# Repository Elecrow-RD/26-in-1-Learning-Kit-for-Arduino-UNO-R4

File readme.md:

## Menu
### 1, Product picture
### 2, Product version number
### 3, product information
### 4, Use the driver module
### 5,Quick Start
### 6,Folder structure.
### 7,Pin definition

### 1, Product picture

#### 2, Product version number

|      | Hardware | Software | Remark |
| ---- | -------- | -------- | ------ |
| 1    | V1.0     | V1.0     | latest |
### 3, product information

| Main Processor        | Arduino UNO R4                                               |
| --------------------- | ------------------------------------------------------------ |
| CPU/SoC               | RA4M1(Arm® Cortex-M4®)                                       |
| System memory         | 32 kB SRAM                                                   |
| Storage               | 256 kB Flash Memory                                          |
| Bluetooth             | Bluetooth 5                                                  |
| Wi-Fi                 | Wi-Fi® support with 802.11 b/g/n standarBit rate at up to 150 Mbps2.4 GHz band |
| Interface             | 6\*D Interfaces<br />4\*A Interfaces<br />4\*I2C Interfaces<br />4\* Pin header<br />2\*3pin connectors<br />1*Stepper Interface |
| Button                | Reset                                                        |
| LED indicator light   | 12*8 LED dot matrix                                          |
| Power input           | 5 V                                                          |
| Shell material        | Plastic Box                                                  |
| Size                  | 278\*200*43（mm）                                            |
| Net Weight            | 600g                                                         |
| Operating temperature | 0°C to 60°C                                                  |
| Storage temperature   | 0°C to 60°C                                                  |

### 4, Use the driver module

| Name     | dependency library                           |
| -------- | -------------------------------------------- |
| IRremote | Arduino-IRremote-master <br />version: 4.5.0 |
| LSM6DS3  | Arduino_LSM6DS3-master<br />version=1.0.3    |
| BH1750   | BH1750<br />version: 1.3.0                   |

### 5,Quick Start
### Arduino IDE starts

1.Download the library files used by this product to the 'libraries' folder.

C:\Users\Documents\Arduino\libraries\

2.Open the Arduino IDE and install the Uno development board.

3.Open the code configuration environment and burn it

### 6,Folder structure.

|--Eagle_SCH&PCB: Contains **Eagle CAD** schematic (`.sch`) and PCB layout (`.brd`) files. These are used for circuit design and PCB manufacturing.

|--Single Module Example:Examples of individual modules.

|--lesson_code: Provides  code and projects to demonstrate how to use the hardware and libraries. These examples help users get started quickly.

|--libraries: Includes necessary libraries required for compiling and running the project. These libraries provide drivers and additional functionalities for the hardware.

### 7,Pin definition

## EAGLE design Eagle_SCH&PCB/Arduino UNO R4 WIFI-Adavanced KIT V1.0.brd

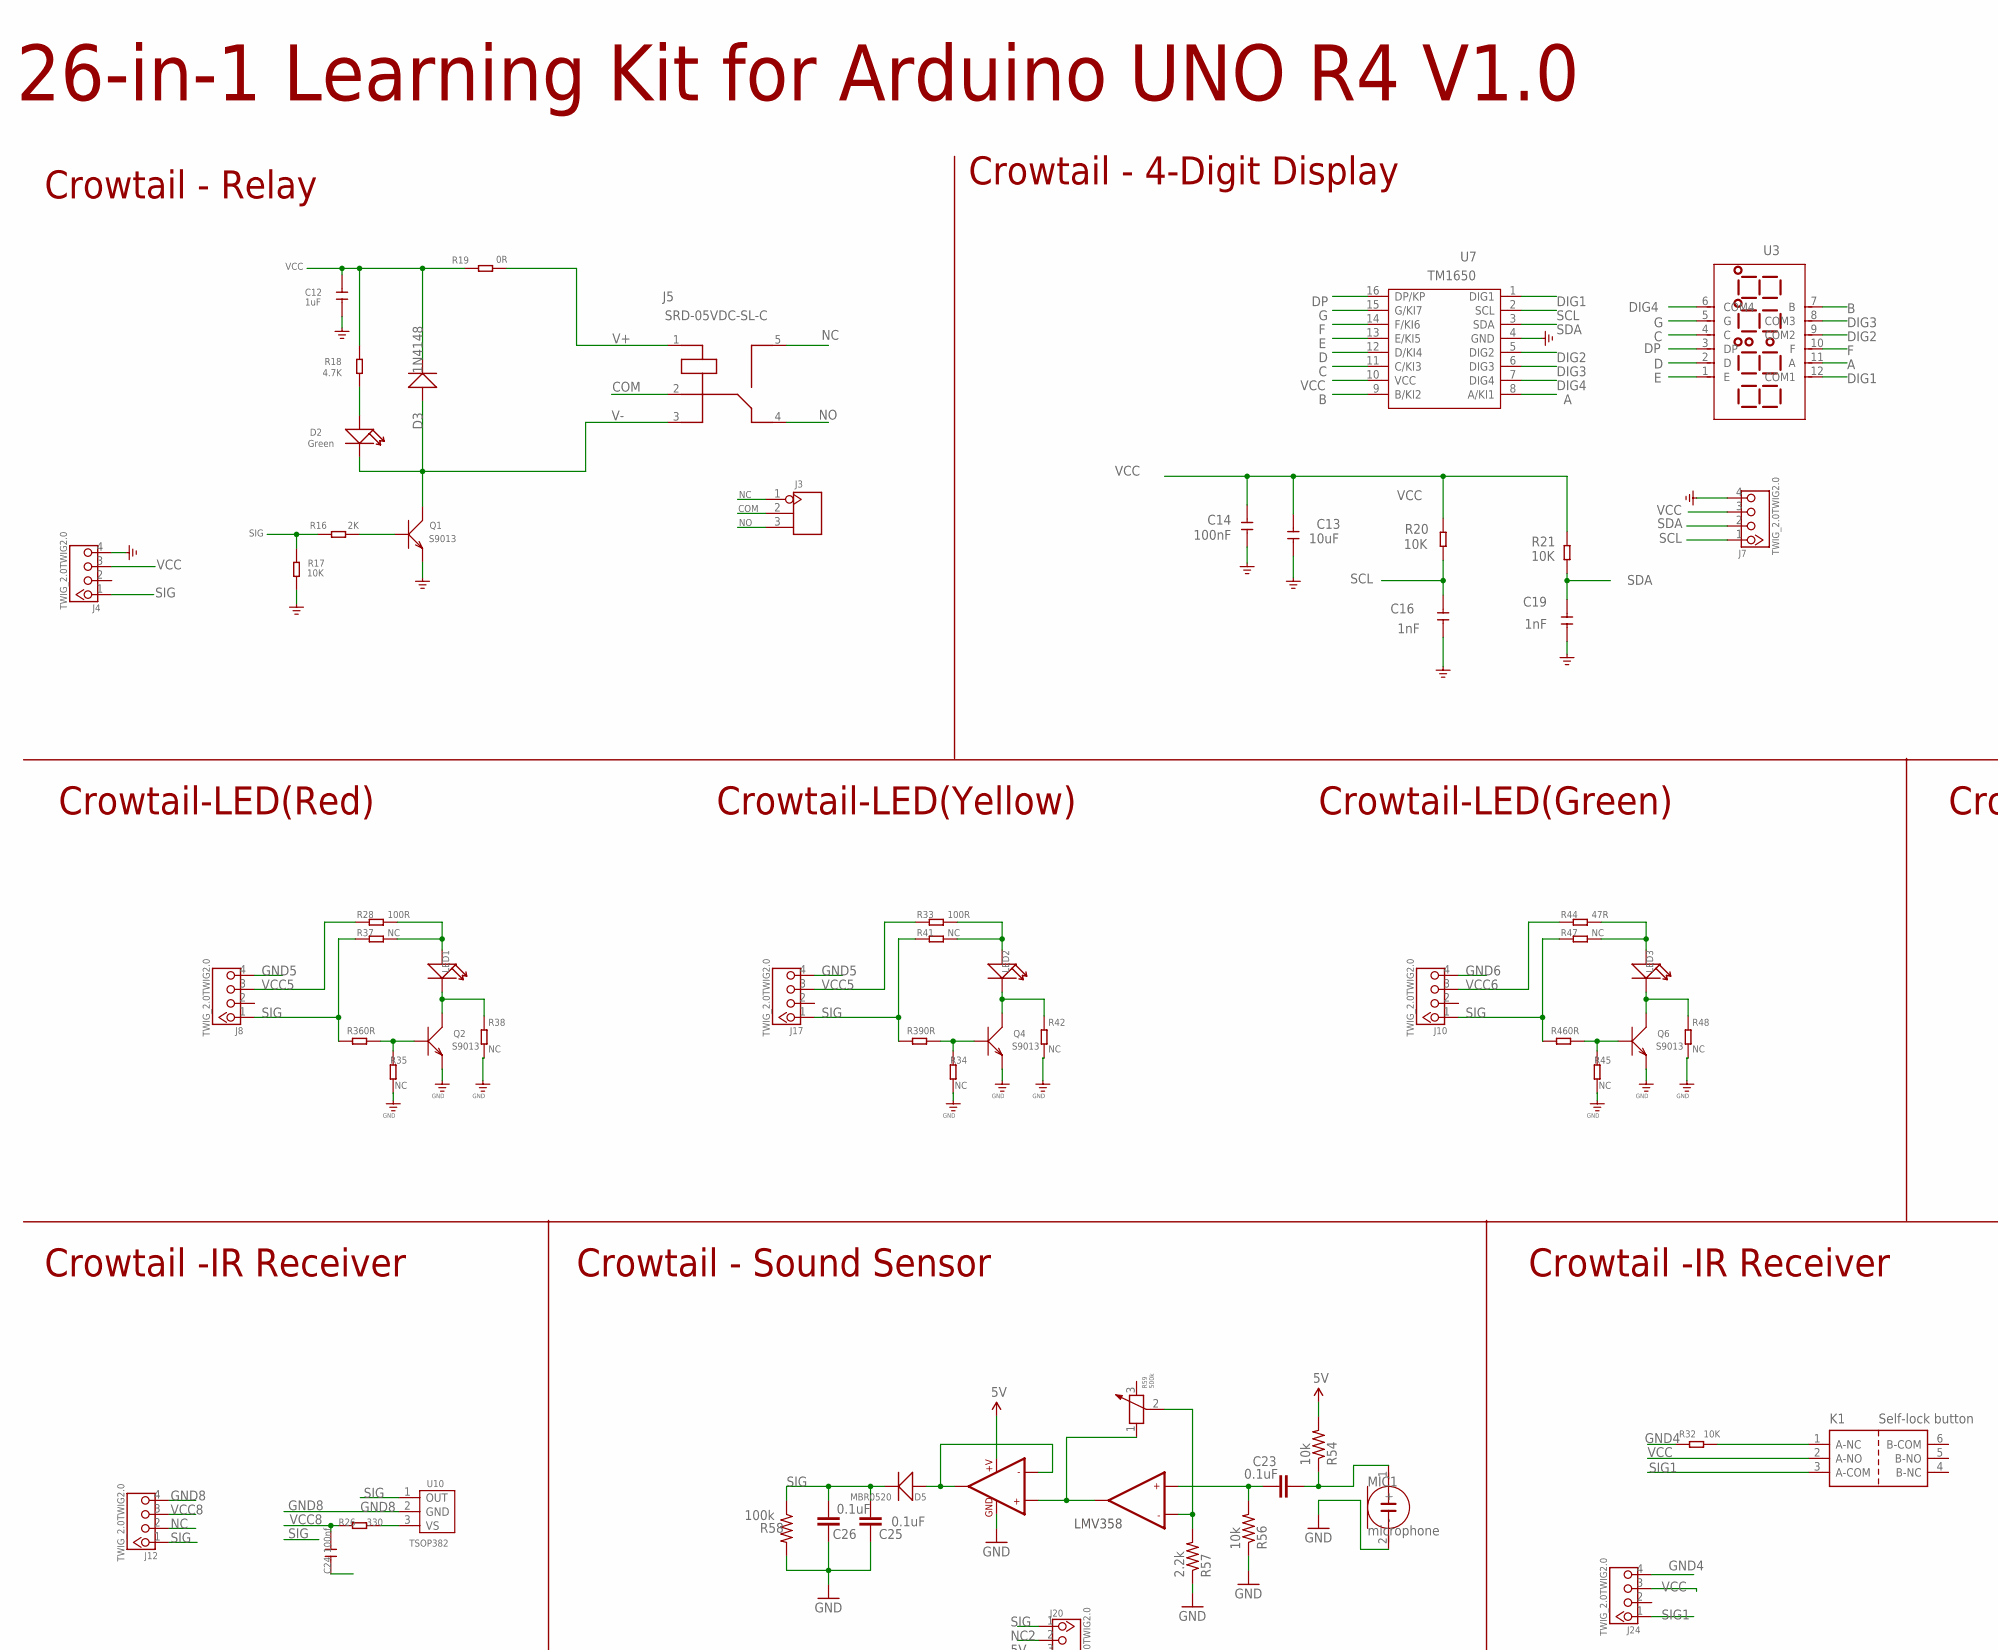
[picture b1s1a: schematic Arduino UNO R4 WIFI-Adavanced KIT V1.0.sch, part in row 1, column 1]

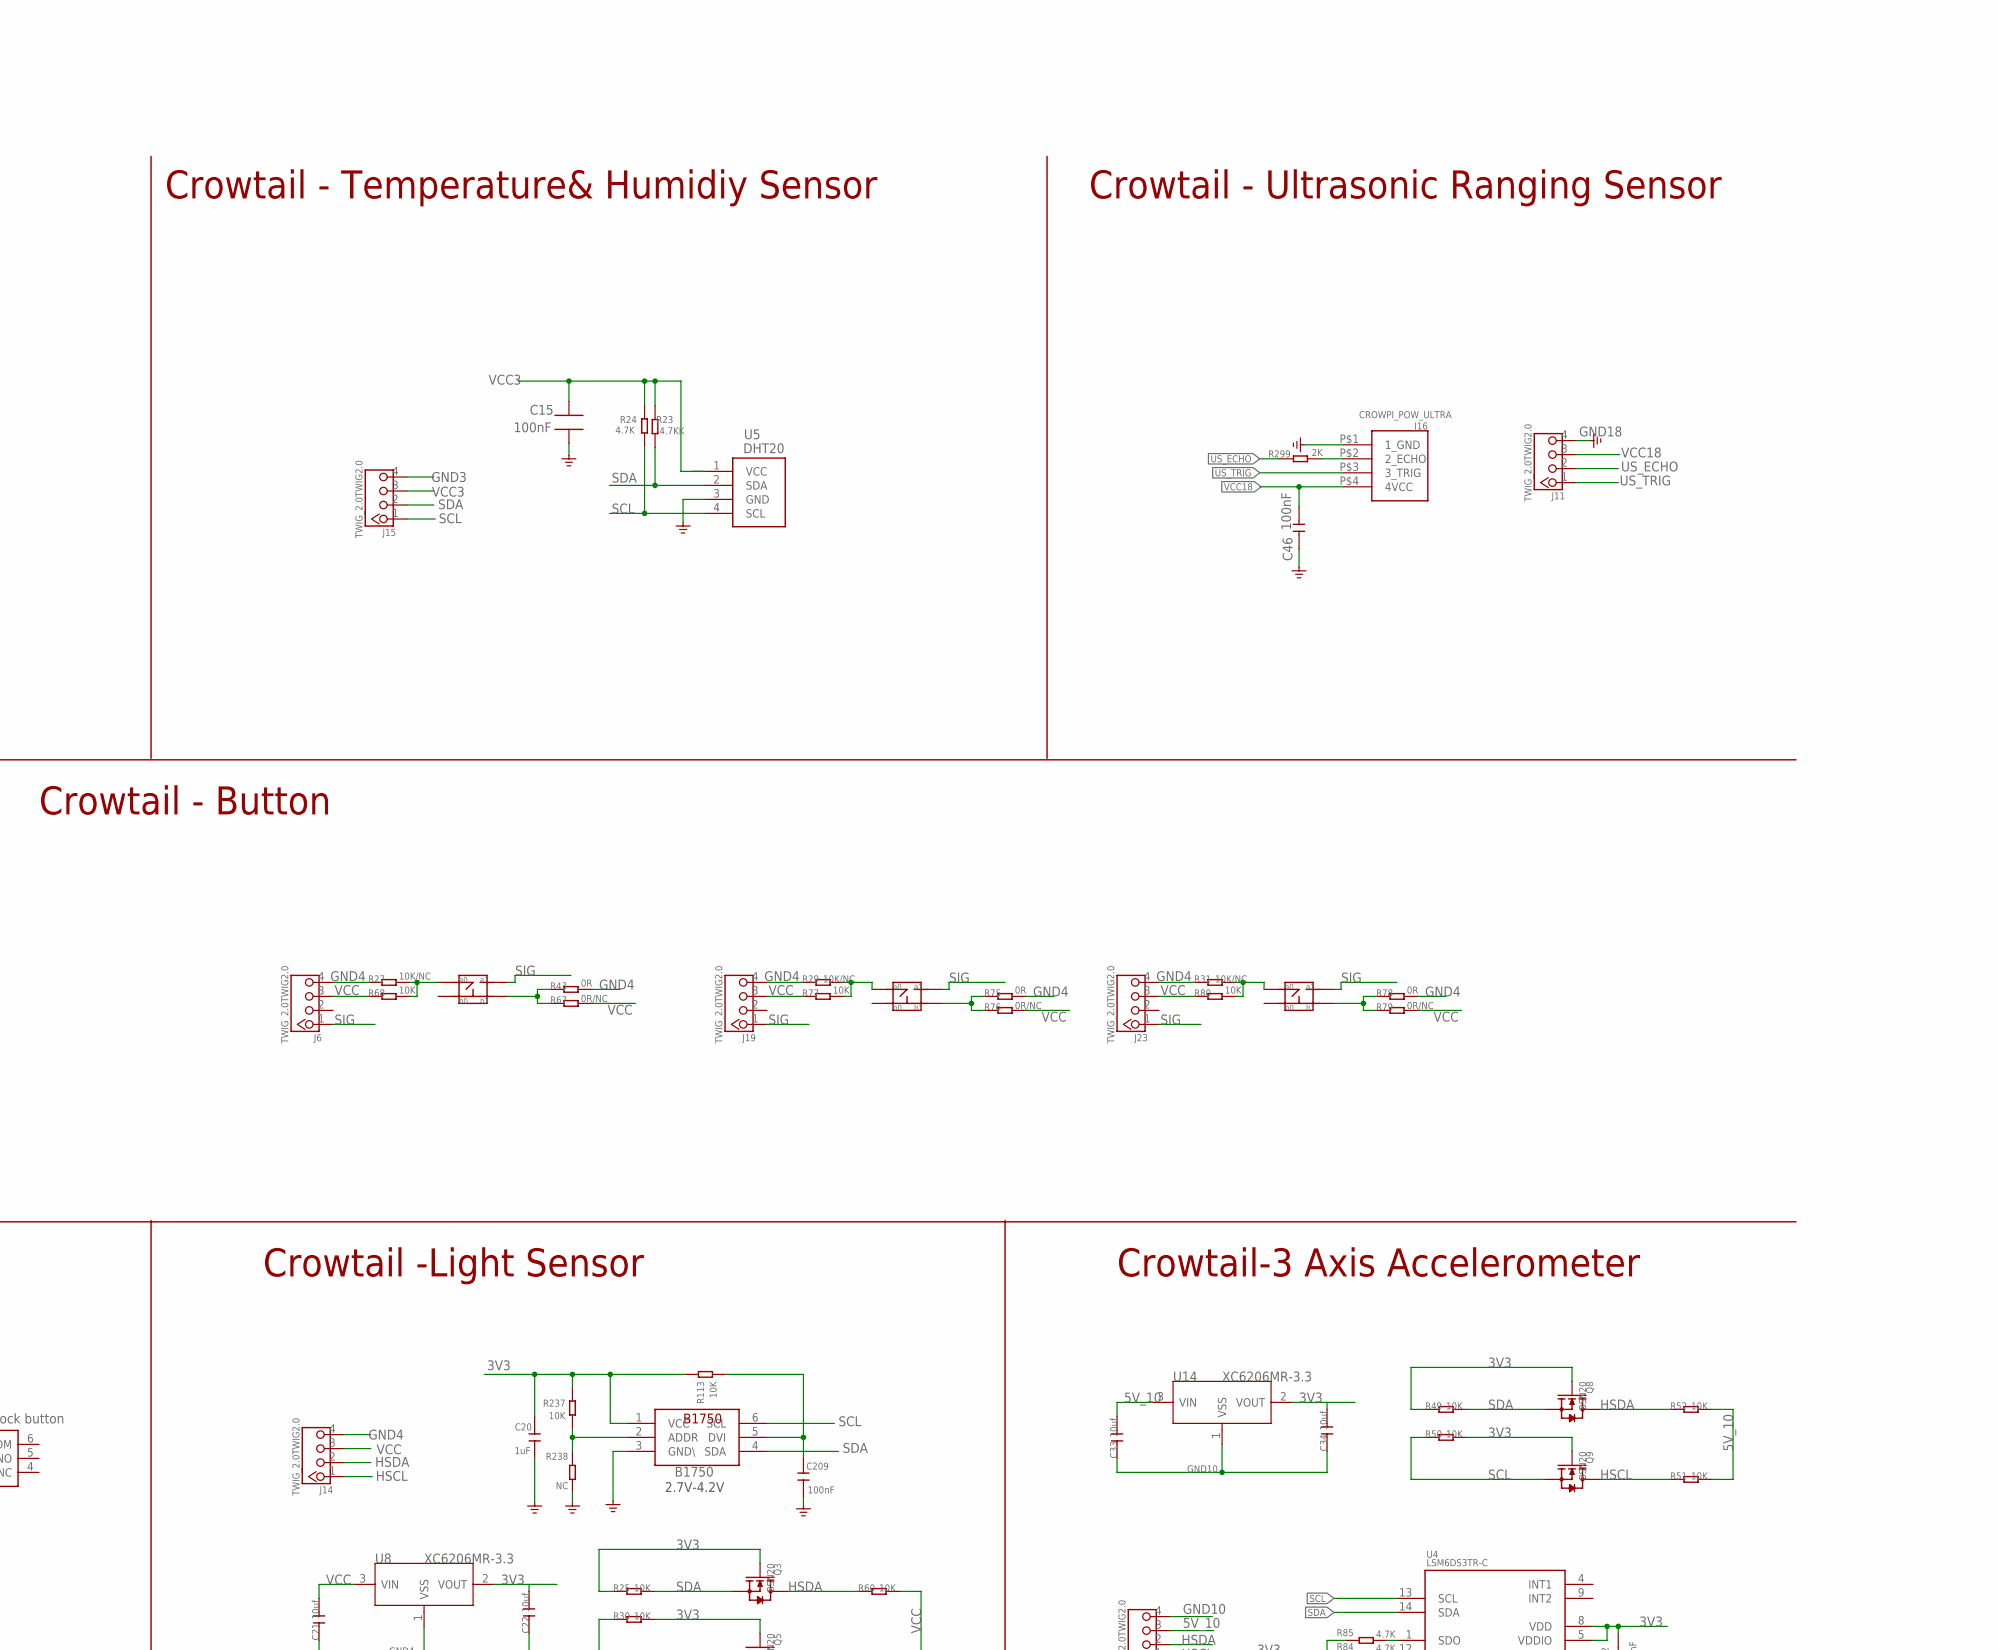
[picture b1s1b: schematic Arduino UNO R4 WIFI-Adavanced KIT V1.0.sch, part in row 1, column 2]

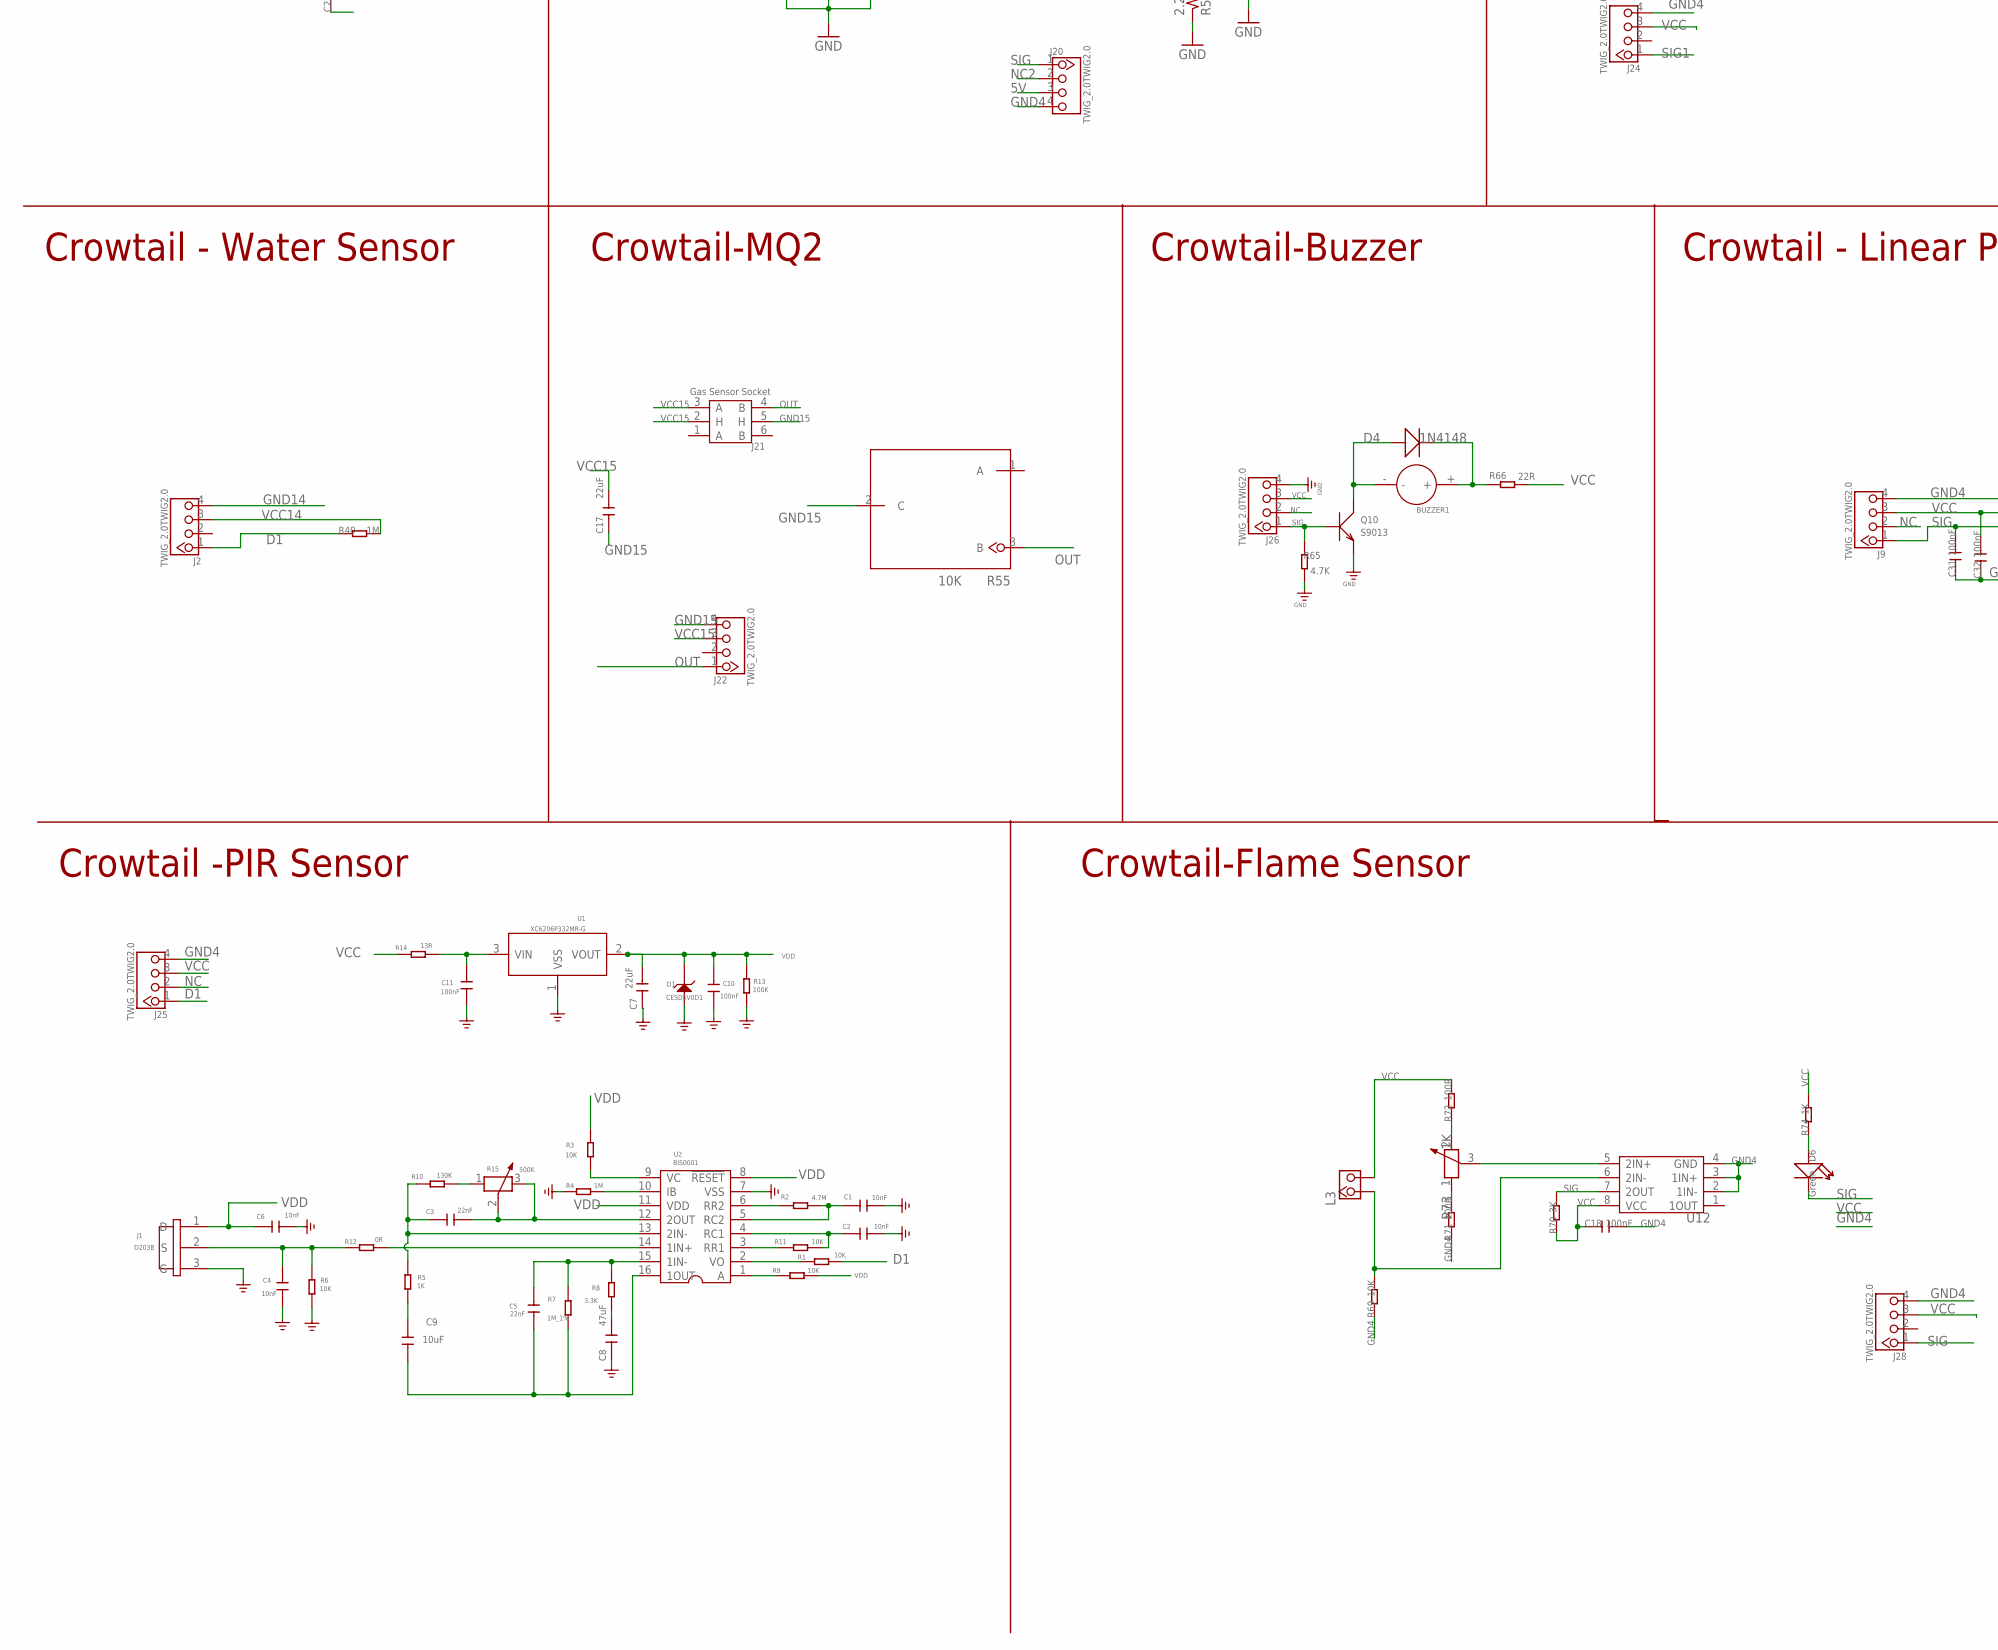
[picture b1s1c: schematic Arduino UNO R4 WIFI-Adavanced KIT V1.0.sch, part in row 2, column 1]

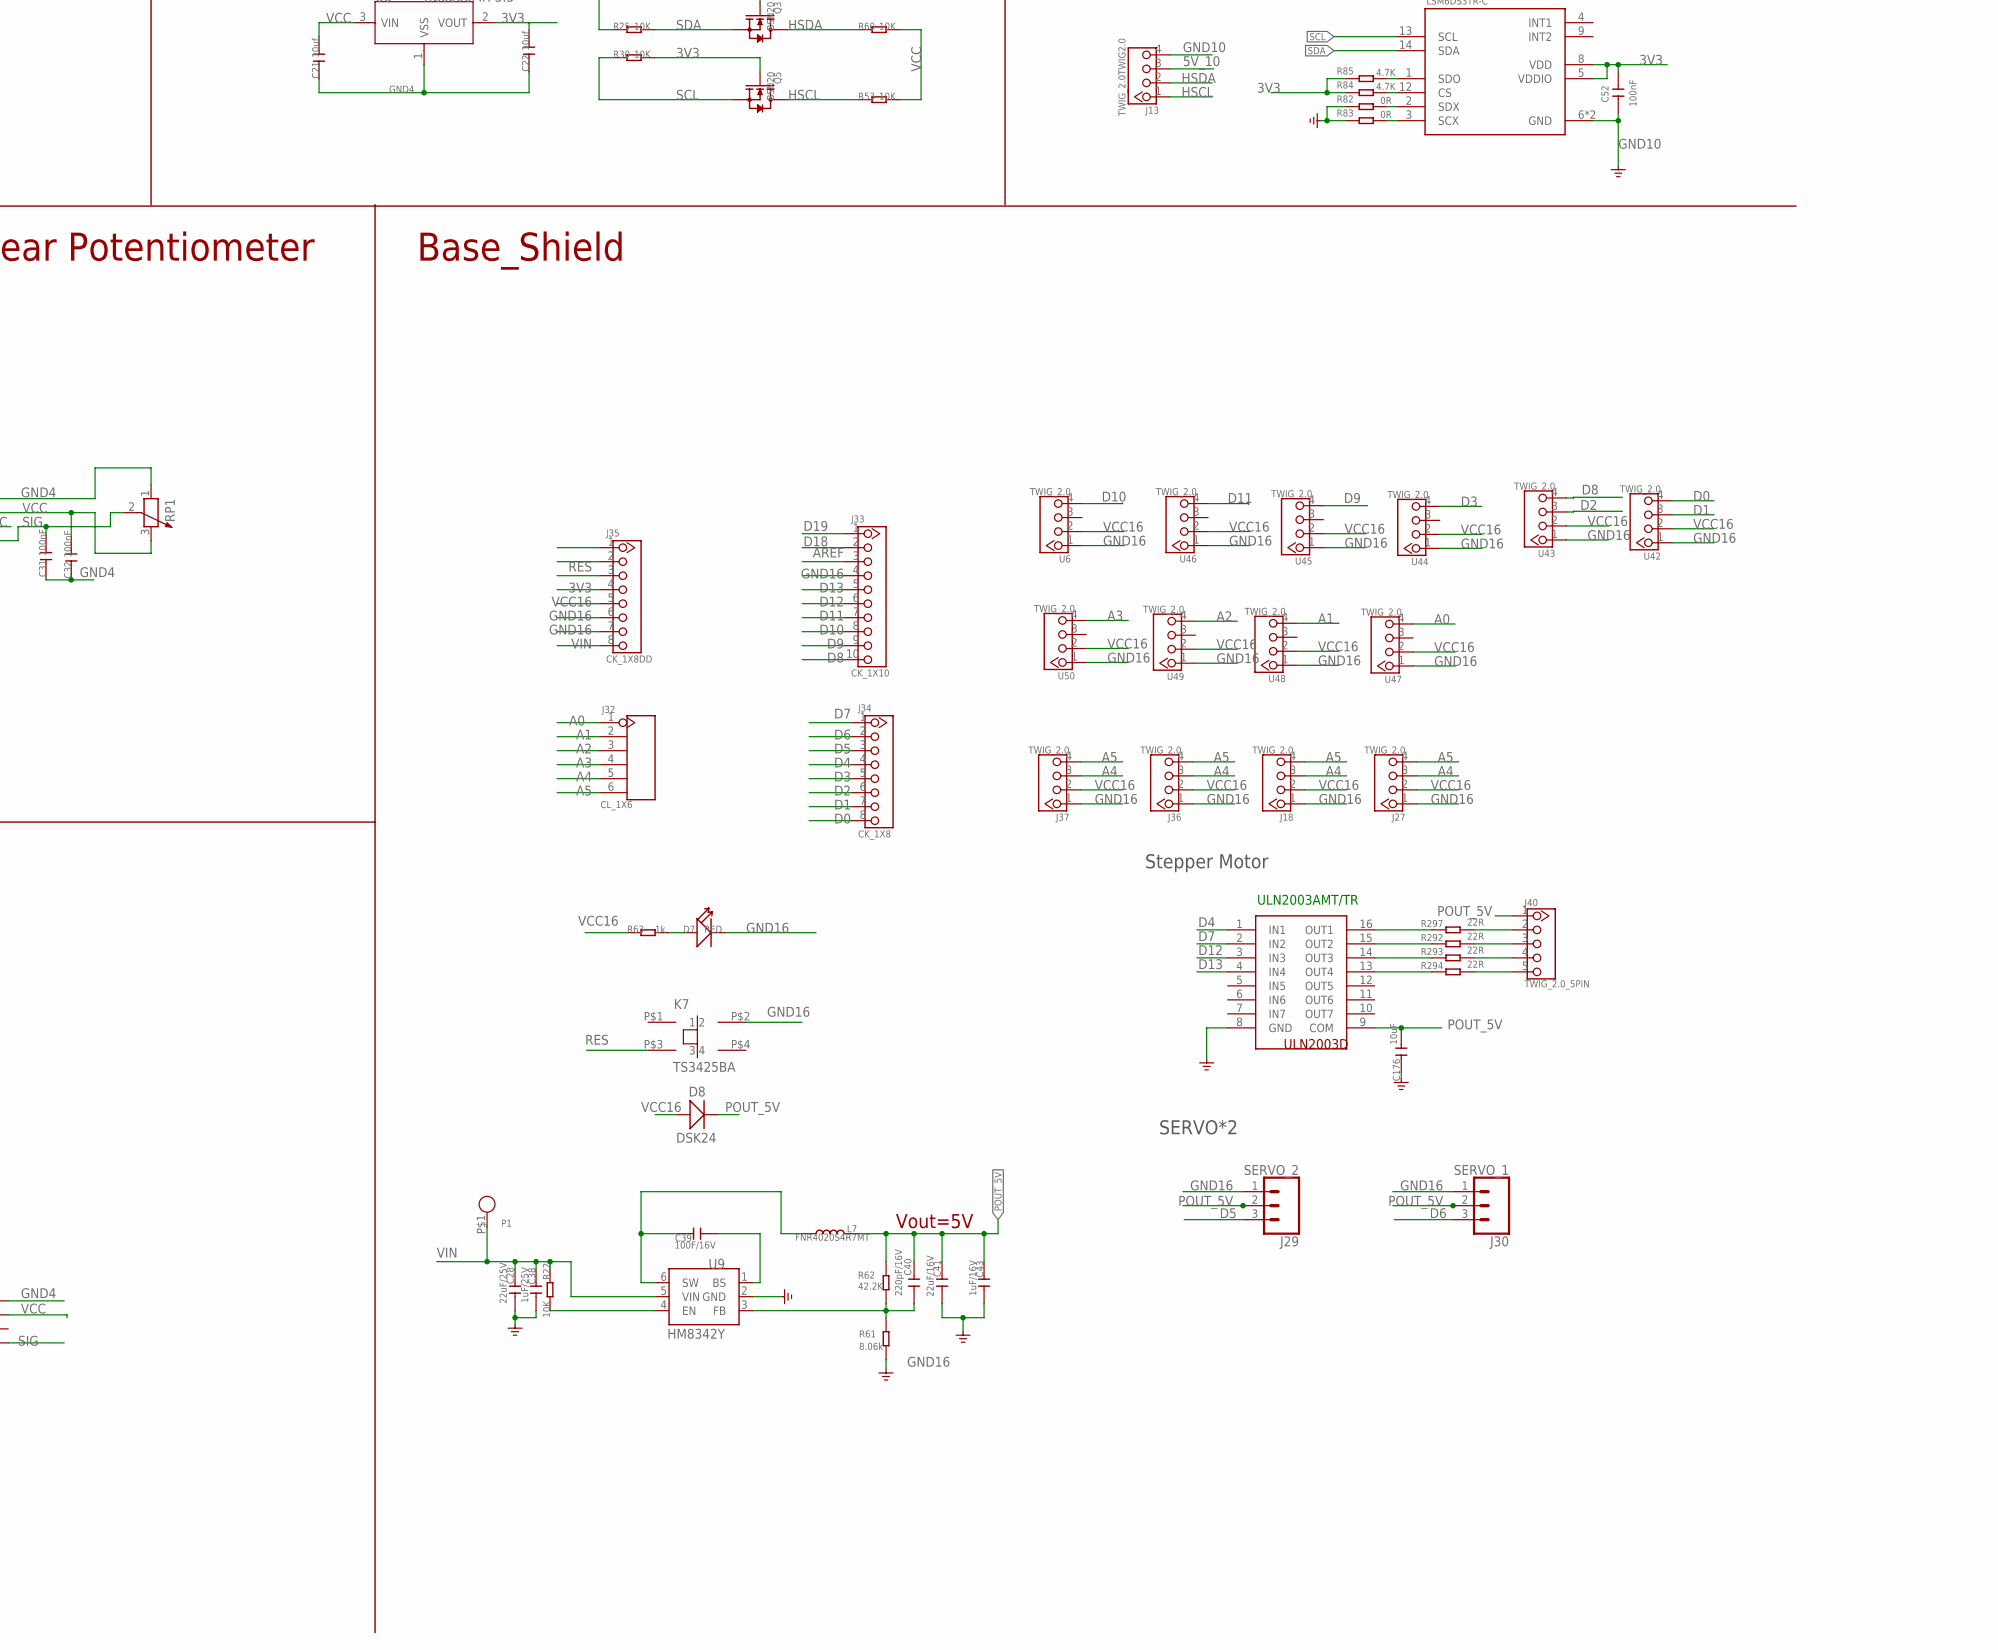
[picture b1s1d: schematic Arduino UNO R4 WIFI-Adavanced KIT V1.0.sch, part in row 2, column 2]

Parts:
BUZZER1: BUZZER-YMD12065; 2P-7.6-D12X6.5H
C1, C2, C4, C6: 10nF; C0603
C3, C5: 22nF; C0603
C7, C17: 22uF; C0805
C8: 47uF; C0805
C9: 10uF; 0603
C10, C11, C14, C18, C31, C32, C46, C52, C209: 100nF; C0603
C12: 1uF; 0603
C13: 10uF; C0603
C15: 100nF; 0603
C16, C19: 1nF; C0603
C20: 1uF; C0603
C21, C22, C33, C34: 10uf; C0603
C23, C25, C26: 0.1uF; 0603-CAP
C24: 100nf; C0603
C28: 22uF/25V; C0805
C38: 1uF/25V; C0603
C39: 100F/16V; C0402
C40: 220pF/16V; C0402
C41: 22uF/16V; C0603
C43: 1uF/16V; C0603
C176: 10uF; C0805
D1: CESD5V0D1; SOD123-2.7X1.6@1
D2, D6: Green; LED-0603
D3, D4: 1N4148; D_SOD123
D5: MBR0520; SOD123-2.7X1.6
D7: RED; LED-0805
D8: DSK24; D_SOD123FL
J1: D203B; 3P-D8.1MM
J2, J4, J6, J7, J8, J9, J10, J11, J12, J13, J14, J15, J17, J19, J20, J22, J23, J24, J25, J26, J28: TWIG_2.0TWIG2.0; TWIG_2.0
J3: SCREW-TERMINAL-3P'5.08'; 3P-5.08
J5: SRD-05VDC-SL-C; A_XBJ_SMART_PUMP_SONGLE_RELAY
J16: CROWPI_POW_ULTRA
J18, J27, J36, J37: TWIG_2.0; 2.0_1X4
J21: Gas Sensor Socket; MQ2
J29: SERVO_2; 1X03
J30: SERVO_1; 1X03
J32: CL_1X6; CK_1X6
J33: CK_1X10
J34: CK_1X8
J35: CK_1X8DD; CK_1X8
J40: TWIG_2.0_5PIN; TWIG-2.0-5PIN
K1: Self-lock button; 6P-2CH-8X8
K2, K3, K4: 12X12
K7: TS3425BA; SMD_KEY4.2*3.*.2.5
L3: HEADER_1X2_2.54; CK_1*2
L7: FNR4020S4R7MT; L_4X4
LED1, LED2, LED3: LED-6MM; LED-2P-2.54-6MM
MIC1: microphone; 2P-D8.9MM
P1: PADPAD-1.0MM; PAD-1.0MM
Q1, Q2, Q4, Q6: S9013; SOT23@1
Q3, Q5, Q8, Q9: BSN20; SOT23@2
Q10: S9013; DISCRETE_SOT23
R1, R3, R6, R9, R11, R17, R20, R21, R25, R30, R32, R49, R50, R51, R52, R53, R60, R68, R69, R77, R80, R113, R237: 10K; R0603
R2: 4.7M; R0603
R4: 1M; R0603
R5, R74: 1K; R0603
R7: 1M_1%; R0603
R8: 3.3K; R0603
R10: 130K; R0603
R12, R19, R36, R39, R43, R46, R75, R78, R82, R83: 0R; R0603
R13: 100K; R0603
R14: 13R; R0603
R15: 500K; 3P-SMD-SQUA-3.6X3.3
R16, R299: 2K; R0603
R18, R65, R84, R85: 4.7K; R0603
R22: 10K; R0402
R23: 4.7KK; 0603
R24: 4.7K; 0603
R26: 330; R0603
R27, R29, R31: 10K/NC; R0603
R28, R33, R71, R72: 100R; R0603
R34, R35, R37, R38, R41, R42, R45, R47, R48, R238: NC; R0603
R40: 1M; 0603
R44: 47R; R0603
R54, R56: 10k; 0603-RES
R55: 10K; PACKAGE__RESISTANCE
R57: 2.2k; 0603-RES
R58: 100k; 0603-RES
R59: 500k; 3P-SMD-SQUA-3.6X3.3
R61: 8.06k; R0402
R62: 42.2K; R0402
R63: 1k; 0603
R66, R292, R293, R294, R297: 22R; R0603
R67, R76, R79: 0R/NC; R0603
R70: 3K; R0603
R73: 1K; 3P-SQUA-7X6.8
RP1: R-POTENTIOMETER; 3P-SQUA-45.6X10X5.8H
U1: XC6206P332MR-G; SOT23
U2: BIS0001; SOP16
U3: MODULE_LED-4BIT-7SEG/CLOCK; MODULE_7-4-SEG/CLOCK-2.54-32.2*10.2*5.8
U4: LSM6DS3TR-C; LGA-14L
U5: DHT20
U6, U42, U43, U44, U45, U46, U47, U48, U49, U50: TWIG_2.0; 2.0_1X4
U7: TM1650; SO16
U8, U14: XC6206MR-3.3; SOT23
U9: HM8342Y; SOT23-6L
U10: TSOP382; 3P-2.54-4.8X5X6.95H
U11: LMV358; SO08
U12: LM293D; SOIC8-6.0
U114: ULN2003AMT/TR; SOP65P640X120-16N
U121: BH1750; B1750

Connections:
3V3: C20.2, C22.2, C34.2, C52.2, J35.4, Q3.1 (G), Q5.1 (G), Q8.1 (G), Q9.1 (G), R25.1, R30.2, R49.1, R50.2, R84.1, R85.1, R113.2, R237.2, U4.5 (VDDIO), U4.8 (VDD), U8.2 (VOUT), U14.2 (VOUT), U121.1 (VCC)
5V: J20.3, R54.2, U11.8 (+V)
5V_10: C33.2, J13.3, R51.2, R52.2, U14.3 (VIN)
A: U3.11 (A), U7.8 (A/KI1)
A0: J32.1, U47.4
A1: J32.2, U48.4
A2: J32.3, U49.4
A3: J32.4, U50.4
A4: J18.3, J27.3, J32.5, J36.3, J37.3
A5: J18.4, J27.4, J32.6, J36.4, J37.4
AREF: J33.3
B: U3.7 (B), U7.9 (B/KI2)
C: U3.4 (C), U7.11 (C/KI3)
COM: J3.2, J5.2
D: U3.2 (D), U7.12 (D/KI4)
D0: J34.8, U42.4
D1: J2.1, J25.1, J34.7, R1.1, R40.1, U42.3
D2: J34.6, U43.3
D3: J34.5, U44.4
D4: J34.4, U114.1 (IN1)
D5: J29.3, J34.3
D6: J30.3, J34.2
D7: J34.1, U114.2 (IN2)
D8: J33.10, U43.4
D9: J33.9, U45.4
D10: J33.8, U6.4
D11: J33.7, U46.4
D12: J33.6, U114.3 (IN3)
D13: J33.5, U114.4 (IN4)
D18: J33.2
D19: J33.1
DIG1: U3.12 (COM1), U7.1 (DIG1)
DIG2: U3.9 (COM2), U7.5 (DIG2)
DIG3: U3.8 (COM3), U7.6 (DIG3)
DIG4: U3.6 (COM4), U7.7 (DIG4)
DP: U3.3 (DP), U7.16 (DP/KP)
E: U3.1 (E), U7.13 (E/KI5)
F: U3.10 (F), U7.14 (F/KI6)
G: U3.5 (G), U7.15 (G/KI7)
GND3: C15.2, J15.4, U5.3 (GND)
GND4: C1.2, C2.2, C4.1, C6.1, C7.1, C8.1, C10.2, C11.1, C12.1, C13.2, C14.2, C16.2, C18.2, C19.2, C20.1, C21.1, C22.1, C25.1, C26.1, C31.1, C32.1, C209.1, D1.1, J1.3 (G), J4.4, J6.4, J7.4, J9.4, J14.4, J19.4, J20.4, J23.4, J24.4, J25.4, J26.4, J28.4, MIC1.2 (-), Q1.2 (E), Q10.2 (E), R4.1, R6.1, R13.2, R17.1, R27.1, R29.1, R31.1, R32.1, R43.2, R56.1, R57.1, R58.2, R65.1, R69.1, R71.1, R75.2, R78.2, R238.1, RP1.1, U1.1 (VSS), U2.7 (VSS), U7.4 (GND), U8.1 (VSS), U11.4 (GND), U12.2 (1IN-), U12.3 (1IN+), U12.4 (GND), U121.3 (GND\)
GND5: J8.4, J17.4, Q2.2 (E), Q4.2 (E), R34.1, R35.1, R38.2, R42.2
GND6: J10.4, Q6.2 (E), R45.1, R48.2
GND8: C24.1, J12.4, U10.2 (GND)
GND10: C33.1, C34.1, C52.1, J13.4, R82.1, R83.1, U4.6 (GND), U4.7 (GND), U14.1 (VSS)
GND14: J2.4
GND15: C17.1, J21.5 (H), J22.4, R55.2 (C)
GND16: C28.1, C38.2, C41.1, C43.2, C176.2, D7.-, J18.1, J27.1, J29.1, J30.1, J33.4, J35.6, J35.7, J36.1, J37.1, K7.P$2 (2), R61.1, U6.1, U9.2 (GND), U42.1, U43.1, U44.1, U45.1, U46.1, U47.1, U48.1, U49.1, U50.1, U114.8 (GND)
GND18: C46.2, J11.4, J16.P$1 (1_GND)
HSCL: J13.1, J14.1, Q5.3 (D), Q9.3 (D), R51.1, R53.1
HSDA: J13.2, J14.2, Q3.3 (D), Q8.3 (D), R52.1, R60.1
unnamed: R82.2, U4.2 (SDX)
unnamed: R26.2, U10.3 (VS)
unnamed: C209.2, R113.1, U121.5 (DVI)
unnamed: K2.P$1, R27.2, R68.2
unnamed: Q1.1 (B), R16.2
unnamed: D2.+, R18.2
unnamed: LED2.+, R33.2, R41.1
unnamed: LED1.+, R28.2, R37.1
unnamed: LED1.-, Q2.3 (C), R38.1
unnamed: Q2.1 (B), R35.2, R36.2
unnamed: R297.1, U114.16 (OUT1)
unnamed: K4.P$1, R31.2, R80.2
unnamed: LED2.-, Q4.3 (C), R42.1
unnamed: R11.1, U2.3 (RR1)
unnamed: LED3.+, R44.2, R47.1
unnamed: C2.1, R11.2, U2.4 (RC1)
unnamed: LED3.-, Q6.3 (C), R48.1
unnamed: Q6.1 (B), R45.2, R46.2
unnamed: R1.2, U2.2 (VO)
unnamed: R2.2, U2.6 (RR2)
unnamed: C1.1, R2.1, U2.5 (RC2)
unnamed: C3.2, R15.2 (3), R15.3 (2), U2.12 (2OUT)
unnamed: C3.1, R5.2, R10.2, U2.13 (2IN-)
unnamed: R3.2, U2.9 (VC)
unnamed: R4.2, U2.10 (IB)
unnamed: C4.2, J1.2 (S), R6.2, R12.2
unnamed: C5.1, C9.2, R7.1, U2.16 (1OUT)
unnamed: C5.2, R7.2, R8.2, U2.15 (1IN-)
unnamed: C9.1, R5.1
unnamed: C8.2, R8.1
unnamed: R9.2, U2.1 (A)
unnamed: R12.1, U2.14 (1IN+)
unnamed: C11.2, R14.1, U1.3 (VIN)
unnamed: R10.1, R15.1
unnamed: Q4.1 (B), R34.2, R39.2
unnamed: K1.1 (A-NC), R32.2
unnamed: R84.2, U4.12 (CS)
unnamed: K2.P$3, R43.1, R67.1
unnamed: R292.1, U114.15 (OUT2)
unnamed: C23.1, MIC1.1 (+), R54.1
unnamed: C23.2, R56.2, U11.5 (+IN2)
unnamed: R57.2, R59.2 (3), U11.6 (-IN2)
unnamed: D5.2 (+), U11.1 (OUT1), U11.2 (-IN1)
unnamed: R59.1, U11.3 (+IN1), U11.7 (OUT2)
unnamed: R293.1, U114.14 (OUT3)
unnamed: R294.1, U114.13 (OUT4)
unnamed: D7.+, R63.2
unnamed: BUZZER1.-, D4.+, Q10.3 (C)
unnamed: BUZZER1.+, D4.-, R66.1
unnamed: R71.2, R73.1
unnamed: R83.2, U4.3 (SCX)
unnamed: R72.1, R73.2
unnamed: R73.3, U12.5 (2IN+)
unnamed: D6.+, R74.1
unnamed: L3.1, R69.2, U12.6 (2IN-)
unnamed: K3.P$1, R29.2, R77.2
unnamed: K3.P$3, R75.1, R76.1
unnamed: R85.2, U4.1 (SDO)
unnamed: R237.1, R238.2, U121.2 (ADDR)
unnamed: J40.2, R297.2
unnamed: J40.3, R292.2
unnamed: J40.4, R293.2
unnamed: J40.5, R294.2
unnamed: J16.P$2 (2_ECHO), R299.1
unnamed: R22.1, U9.4 (EN)
unnamed: C39.1, L7.1, U9.6 (SW)
unnamed: C39.2, U9.1 (BS)
unnamed: C40.1, R61.2, R62.1, U9.3 (FB)
unnamed: K4.P$3, R78.1, R79.1
NC: J3.1, J5.5, J9.2, J12.2, J25.2, J26.2
NC2: J20.2
NO: J3.3, J5.4
OUT: J21.4 (B), J22.1, R55.3 (B)
POUT_5V: C40.2, C41.2, C43.1, C176.1, D8.-, J29.2, J30.2, J40.1, L7.2, R62.2, U114.9 (COM)
RES: J35.3, K7.P$3 (3)
SCL: C16.1, J7.1, J15.1, Q5.2 (S), Q9.2 (S), R20.2, R24.1, R30.1, R50.1, U4.13 (SCL), U5.4 (SCL), U7.2 (SCL), U121.6 (SCL)
SDA: C19.1, J7.2, J15.2, Q3.2 (S), Q8.2 (S), R21.2, R23.1, R25.2, R49.2, U4.14 (SDA), U5.2 (SDA), U7.3 (SDA), U121.4 (SDA)
SIG: C25.2, C26.2, C31.2, D5.1 (-), D6.-, J4.1, J6.1, J8.1, J9.1, J10.1, J12.1, J17.1, J19.1, J20.1, J23.1, J26.1, J28.1, K2.P$2, K3.P$2, K4.P$2, Q10.1 (B), R16.1, R17.2, R36.1, R37.2, R39.1, R41.2, R46.1, R47.2, R58.1, R65.2, R70.2, RP1.2 (3), U10.1 (OUT), U12.7 (2OUT)
SIG1: J24.1, K1.3 (A-COM)
US_ECHO: J11.2, R299.2
US_TRIG: J11.1, J16.P$3 (3_TRIG)
V+: J5.1, R19.2
V-: D2.-, D3.+, J5.3, Q1.3 (C)
VCC: C12.2, C13.1, C14.1, C18.1, C21.2, C32.2, D3.-, J4.3, J6.3, J7.3, J9.3, J14.3, J19.3, J23.3, J24.3, J25.3, J26.3, J28.3, K1.2 (A-NO), L3.2, R14.2, R18.1, R19.1, R20.1, R21.1, R53.2, R60.2, R66.2, R67.2, R68.1, R70.1, R72.2, R74.2, R76.2, R77.1, R79.2, R80.1, RP1.3 (2), U7.10 (VCC), U8.3 (VIN), U12.8 (VCC)
VCC3: C15.1, J15.3, R23.2, R24.2, U5.1 (VCC)
VCC5: J8.3, J17.3, R28.1, R33.1
VCC6: J10.3, R44.1
VCC8: C24.2, J12.3, R26.1
VCC14: J2.3, R40.2
VCC15: C17.2, J21.2 (H), J21.3 (A), J22.3
VCC16: D8.+, J18.2, J27.2, J35.5, J36.2, J37.2, R63.1, U6.2, U42.2, U43.2, U44.2, U45.2, U46.2, U47.2, U48.2, U49.2, U50.2
VCC18: C46.1, J11.3, J16.P$4 (4VCC)
VDD: C6.2, C7.2, C10.1, D1.2, J1.1 (D), R3.1, R9.1, R13.1, U1.2 (VOUT), U2.8 (!RESET), U2.11 (VDD)
VIN: C28.2, C38.1, J35.8, P1.P$1, R22.2, U9.5 (VIN)

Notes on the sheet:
Crowtail -PIR Sensor
Crowtail - Temperature& Humidiy Sensor
Crowtail-LED(Red)
Crowtail -IR Receiver
Crowtail-3 Axis Accelerometer
Crowtail - Water Sensor
Crowtail-MQ2
Crowtail - Ultrasonic Ranging Sensor
LMV358
2.7V-4.2V
Stepper Motor
ULN2003AMT/TR
SERVO*2
Crowtail - Relay
Crowtail - 4-Digit Display
Crowtail-LED(Yellow)
Crowtail-LED(Green)
Crowtail - Button
Crowtail - Sound Sensor
Crowtail -Light Sensor
Crowtail-Flame Sensor
Crowtail-Buzzer
Crowtail - Linear Potentiometer
Base_Shield
Vout=5V
26-in-1 Learning Kit for Arduino UNO R4 V1.0

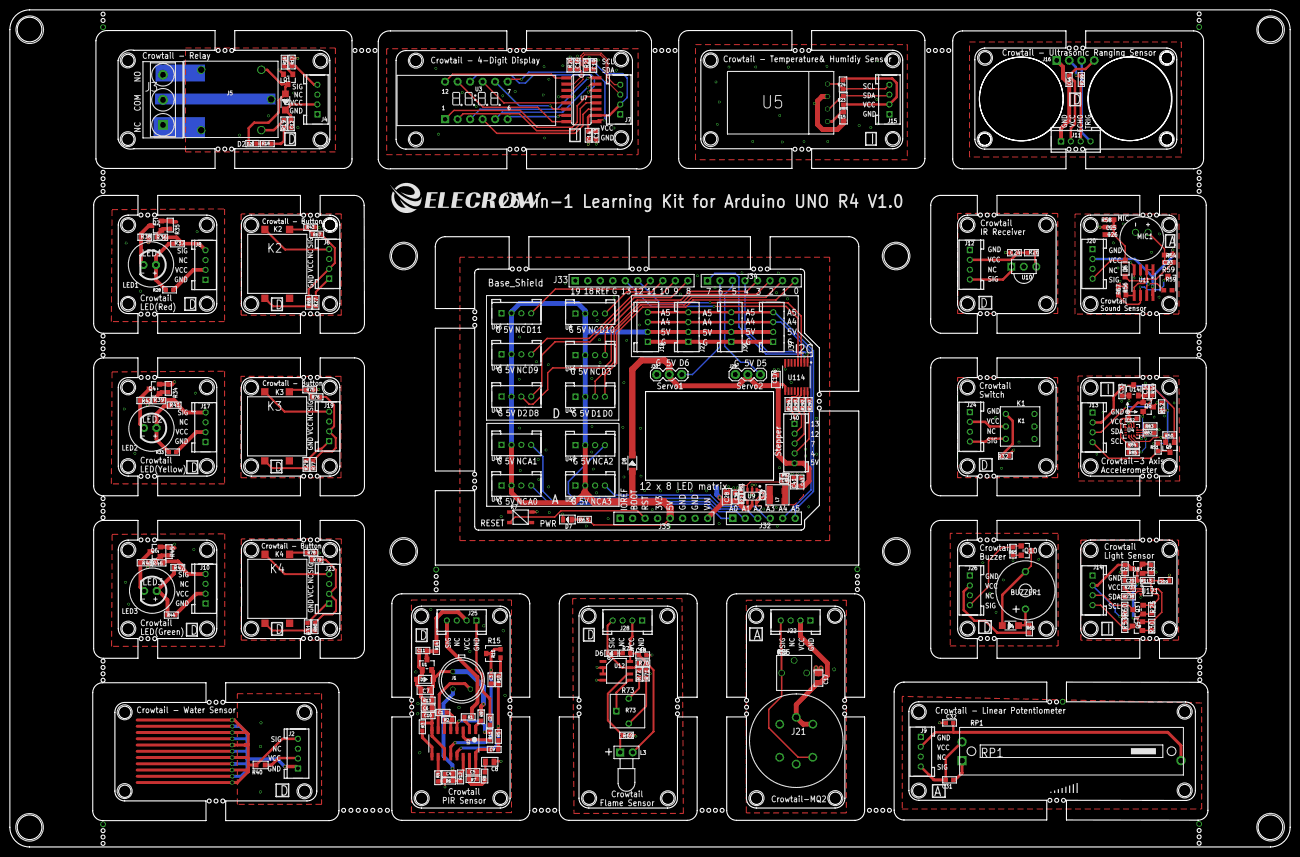
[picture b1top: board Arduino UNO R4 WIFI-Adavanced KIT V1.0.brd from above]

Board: 2 copper layers, 259.9 x 169.9 mm, 223 parts (1 on the bottom side), 140 nets.

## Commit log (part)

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2026-05-05 Update readme.md with formatted content

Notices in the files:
parts and their libraries:
SparkFun-Connectors: Licensing: Creative Commons ShareAlike 4.0 International - https://creativecommons.org/licenses/by-sa/4.0
